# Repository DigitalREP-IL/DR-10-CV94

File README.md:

This is a tile-able design to drive a 25-pixel matrix of Cree CV-94 LED clusters. These are typically used in outdoor and longer distance applications, so the visual separation of the R,G, and B LEDs is not noticeable. The board is laid out such that four can be clustered together and maintain a regular pixel spacing. The onboard driver is I2C addressable but not pre-programmed so an external controller is necessary. Example code for the Arduino environment (easily portable to other frameworks) on a Raspberry Pi Pico (RP2040) is available.

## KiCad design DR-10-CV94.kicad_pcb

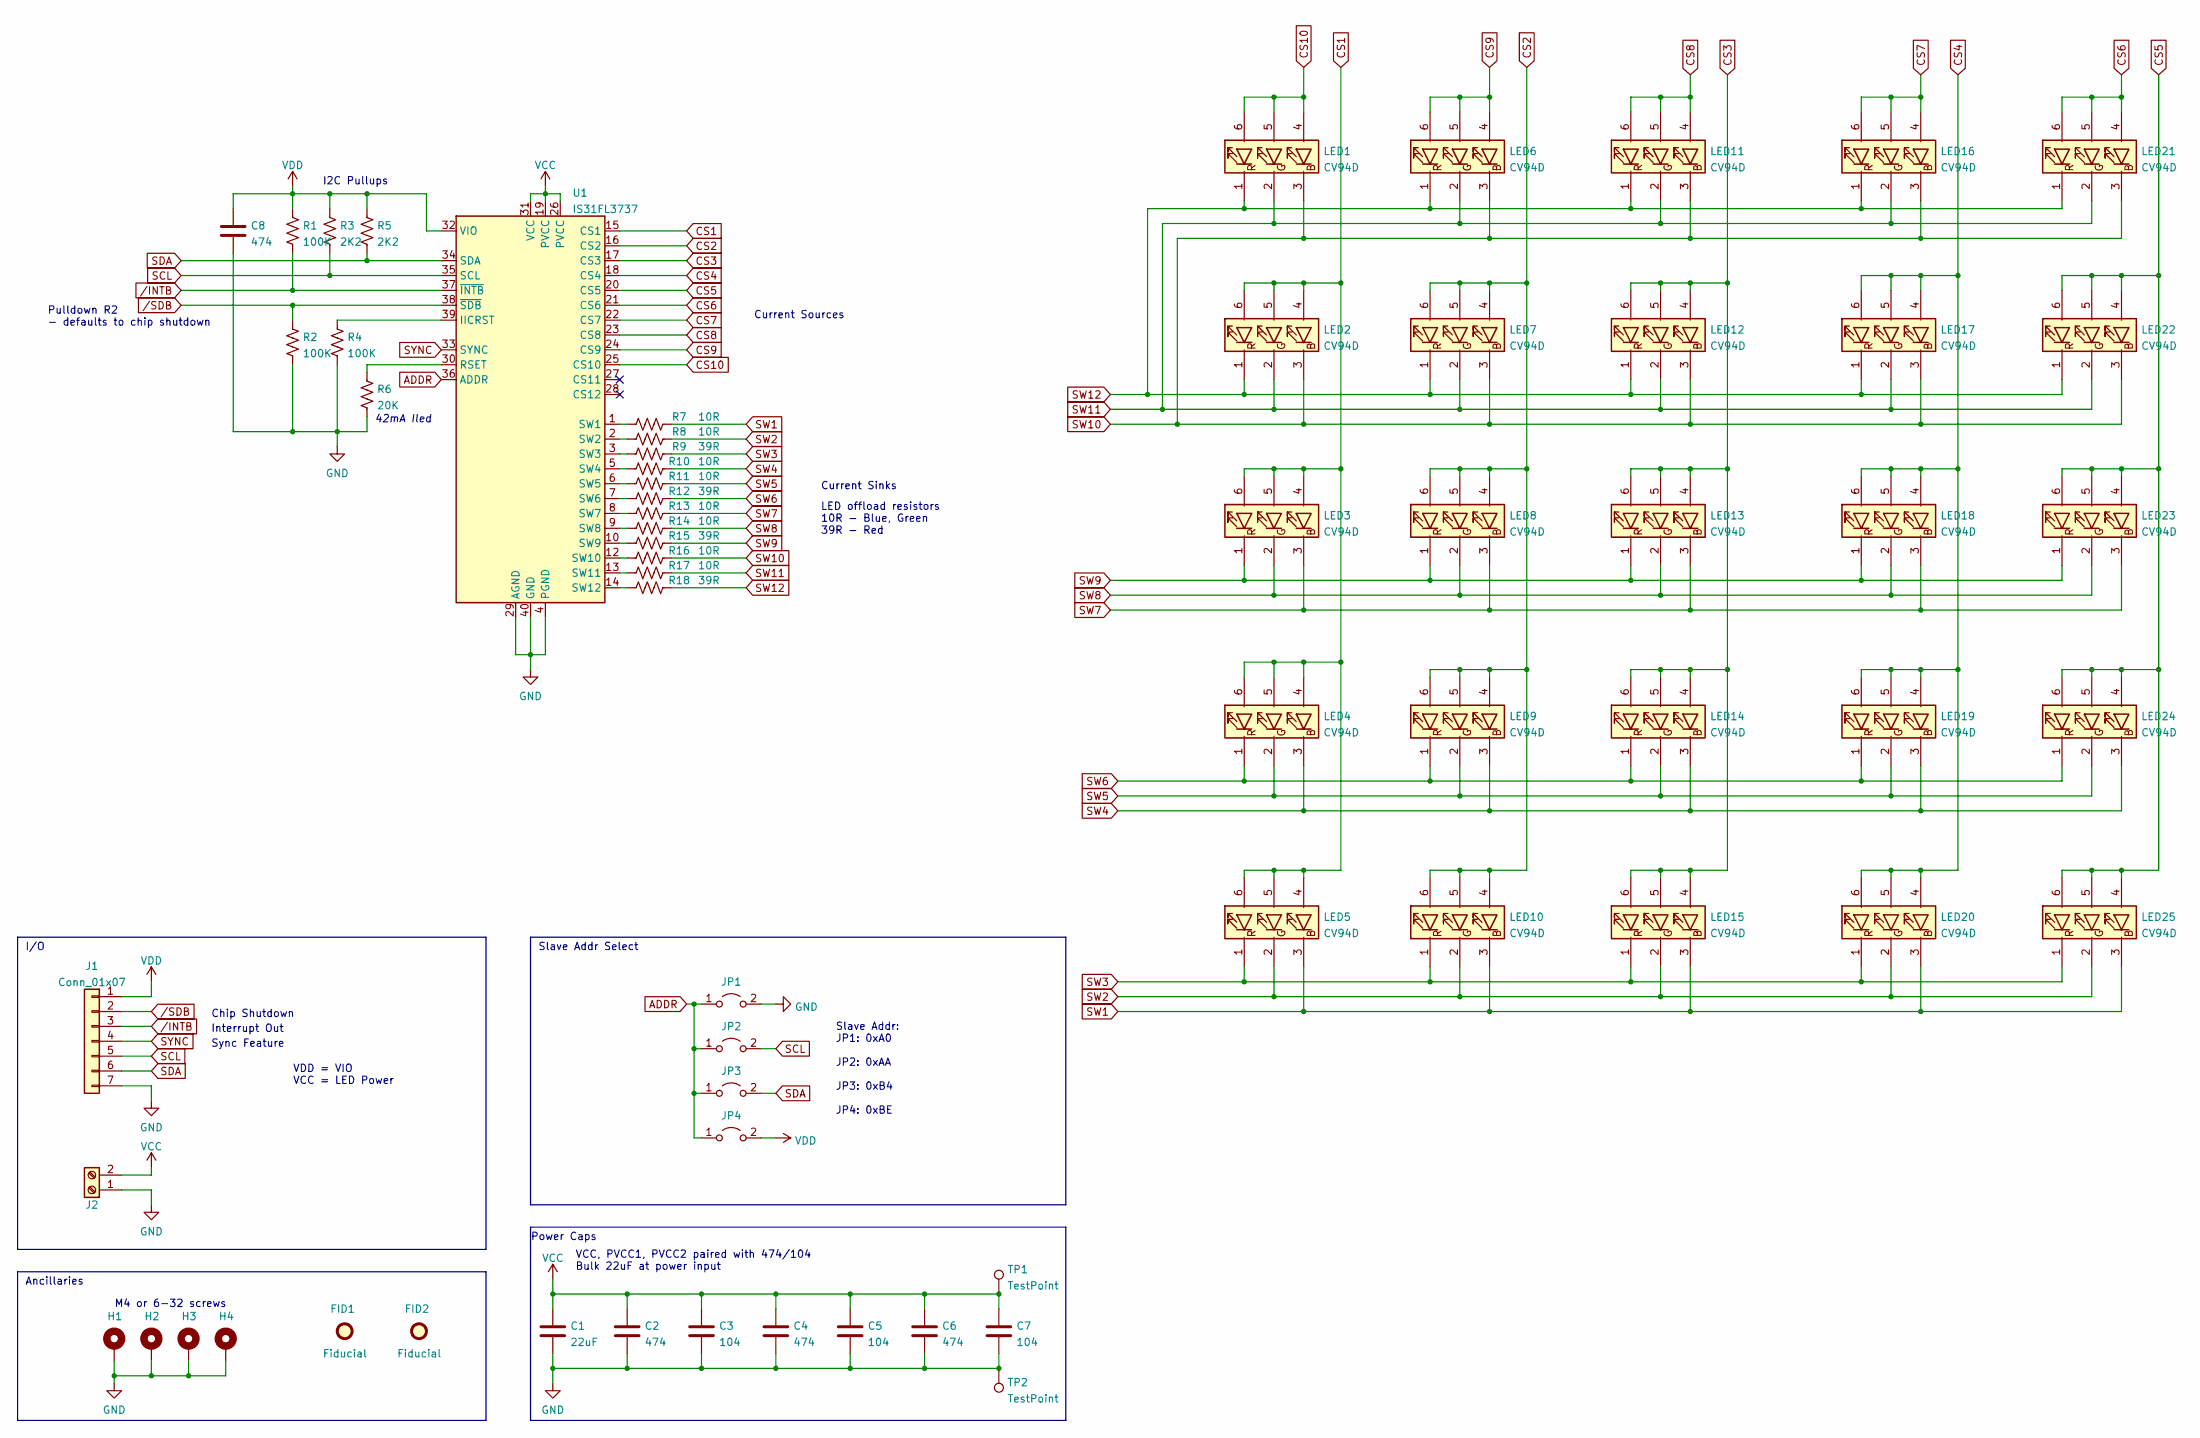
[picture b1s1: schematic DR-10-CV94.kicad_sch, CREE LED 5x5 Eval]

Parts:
C1: 22uF; CP_Elec_4x4.5
C2, C4, C6, C8: 474; C_0805_2012Metric
C3, C5, C7: 104; C_0805_2012Metric
FID1, FID2: Fiducial; Fiducial_0.5mm_Mask1mm
H1, H2, H3, H4: MountingHole_Pad; MountingHole_4.3mm_M4_ISO7380_Pad_TopBottom
J1: Conn_01x07; PinHeader_1x07_P2.54mm_Horizontal
J2: Screw_Terminal_01x02; TerminalBlock_Phoenix_MPT-0,5-2-2.54_1x02_P2.54mm_Horizontal
JP1, JP2, JP3, JP4: Jumper_2_Open; PinHeader_1x02_P2.54mm_Vertical
LED1, LED2, LED3, LED4, LED5, LED6, LED7, LED8, LED9, LED10, LED11, LED12, LED13, LED14, LED15, LED16, LED17, LED18, LED19, LED20, LED21, LED22, LED23, LED24, LED25: CV94D; LED_CREE_PLCC6_3n1
R1, R2, R4: 100K; R_0603_1608Metric
R3, R5: 2K2; R_0603_1608Metric
R6: 20K; R_0805_2012Metric
R7, R8, R10, R11, R13, R14, R16, R17: 10R; R_0603_1608Metric
R9, R12, R15, R18: 39R; R_0603_1608Metric
TP1, TP2: TestPoint; TestPoint_Pad_D2.5mm
U1: IS31FL3737; QFN-40-1EP_5x5mm_P0.4mm_EP3.8x3.8mm

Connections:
ADDR: JP1.1 (A), JP2.1 (A), JP3.1 (A), JP4.1 (A), U1.36 (ADDR)
CS1: LED2.4 (BA), LED2.5 (GA), LED2.6 (RA), LED3.4 (BA), LED3.5 (GA), LED3.6 (RA), LED4.4 (BA), LED4.5 (GA), LED4.6 (RA), LED5.4 (BA), LED5.5 (GA), LED5.6 (RA), U1.15 (CS1)
CS2: LED7.4 (BA), LED7.5 (GA), LED7.6 (RA), LED8.4 (BA), LED8.5 (GA), LED8.6 (RA), LED9.4 (BA), LED9.5 (GA), LED9.6 (RA), LED10.4 (BA), LED10.5 (GA), LED10.6 (RA), U1.16 (CS2)
CS3: LED12.4 (BA), LED12.5 (GA), LED12.6 (RA), LED13.4 (BA), LED13.5 (GA), LED13.6 (RA), LED14.4 (BA), LED14.5 (GA), LED14.6 (RA), LED15.4 (BA), LED15.5 (GA), LED15.6 (RA), U1.17 (CS3)
CS4: LED17.4 (BA), LED17.5 (GA), LED17.6 (RA), LED18.4 (BA), LED18.5 (GA), LED18.6 (RA), LED19.4 (BA), LED19.5 (GA), LED19.6 (RA), LED20.4 (BA), LED20.5 (GA), LED20.6 (RA), U1.18 (CS4)
CS5: LED22.4 (BA), LED22.5 (GA), LED22.6 (RA), LED23.4 (BA), LED23.5 (GA), LED23.6 (RA), LED24.4 (BA), LED24.5 (GA), LED24.6 (RA), LED25.4 (BA), LED25.5 (GA), LED25.6 (RA), U1.20 (CS5)
CS6: LED21.4 (BA), LED21.5 (GA), LED21.6 (RA), U1.21 (CS6)
CS7: LED16.4 (BA), LED16.5 (GA), LED16.6 (RA), U1.22 (CS7)
CS8: LED11.4 (BA), LED11.5 (GA), LED11.6 (RA), U1.23 (CS8)
CS9: LED6.4 (BA), LED6.5 (GA), LED6.6 (RA), U1.24 (CS9)
CS10: LED1.4 (BA), LED1.5 (GA), LED1.6 (RA), U1.25 (CS10)
GND: C1.2, C2.2, C3.2, C4.2, C5.2, C6.2, C7.2, C8.2, H1.1, H2.1, H3.1, H4.1, J1.7, J2.1, JP1.2 (B), R2.2, R4.2, R6.2, TP2.1, U1.4 (PGND), U1.11 (PGND), U1.29 (AGND), U1.40 (GND), U1.41 (GND)
unnamed: R4.1, U1.39 (IICRST)
unnamed: R6.1, U1.30 (RSET)
unnamed: R7.1, U1.1 (SW1)
unnamed: R8.1, U1.2 (SW2)
unnamed: R9.1, U1.3 (SW3)
unnamed: R10.1, U1.5 (SW4)
unnamed: R11.1, U1.6 (SW5)
unnamed: R12.1, U1.7 (SW6)
unnamed: R13.1, U1.8 (SW7)
unnamed: R14.1, U1.9 (SW8)
unnamed: R15.1, U1.10 (SW9)
unnamed: R16.1, U1.12 (SW10)
unnamed: R17.1, U1.13 (SW11)
unnamed: R18.1, U1.14 (SW12)
SCL: J1.5, JP2.2 (B), R3.2, U1.35 (SCL)
SDA: J1.6, JP3.2 (B), R5.2, U1.34 (SDA)
SW1: LED5.3 (BK), LED10.3 (BK), LED15.3 (BK), LED20.3 (BK), LED25.3 (BK), R7.2
SW2: LED5.2 (GK), LED10.2 (GK), LED15.2 (GK), LED20.2 (GK), LED25.2 (GK), R8.2
SW3: LED5.1 (RK), LED10.1 (RK), LED15.1 (RK), LED20.1 (RK), LED25.1 (RK), R9.2
SW4: LED4.3 (BK), LED9.3 (BK), LED14.3 (BK), LED19.3 (BK), LED24.3 (BK), R10.2
SW5: LED4.2 (GK), LED9.2 (GK), LED14.2 (GK), LED19.2 (GK), LED24.2 (GK), R11.2
SW6: LED4.1 (RK), LED9.1 (RK), LED14.1 (RK), LED19.1 (RK), LED24.1 (RK), R12.2
SW7: LED3.3 (BK), LED8.3 (BK), LED13.3 (BK), LED18.3 (BK), LED23.3 (BK), R13.2
SW8: LED3.2 (GK), LED8.2 (GK), LED13.2 (GK), LED18.2 (GK), LED23.2 (GK), R14.2
SW9: LED3.1 (RK), LED8.1 (RK), LED13.1 (RK), LED18.1 (RK), LED23.1 (RK), R15.2
SW10: LED1.3 (BK), LED2.3 (BK), LED6.3 (BK), LED7.3 (BK), LED11.3 (BK), LED12.3 (BK), LED16.3 (BK), LED17.3 (BK), LED21.3 (BK), LED22.3 (BK), R16.2
SW11: LED1.2 (GK), LED2.2 (GK), LED6.2 (GK), LED7.2 (GK), LED11.2 (GK), LED12.2 (GK), LED16.2 (GK), LED17.2 (GK), LED21.2 (GK), LED22.2 (GK), R17.2
SW12: LED1.1 (RK), LED2.1 (RK), LED6.1 (RK), LED7.1 (RK), LED11.1 (RK), LED12.1 (RK), LED16.1 (RK), LED17.1 (RK), LED21.1 (RK), LED22.1 (RK), R18.2
SYNC: J1.4, U1.33 (SYNC)
VCC: C1.1, C2.1, C3.1, C4.1, C5.1, C6.1, C7.1, J2.2, TP1.1, U1.19 (PVCC), U1.26 (PVCC), U1.31 (VCC)
VDD: C8.1, J1.1, JP4.2 (B), R1.1, R3.1, R5.1, U1.32 (VIO)
/INTB: J1.3, R1.2, U1.37 (~INTB)
/SDB: J1.2, R2.1, U1.38 (~SDB)

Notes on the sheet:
LED offload resistors 10R - Blue, Green 39R - Red
Slave Addr: JP1: 0xA0 JP2: 0xAA JP3: 0xB4 JP4: 0xBE
Sync Feature
Interrupt Out
I/O
Power Caps
Pulldown R2 - defaults to chip shutdown
Ancillaries
Current Sinks
42mA Iled
VCC, PVCC1, PVCC2 paired with 474/104 Bulk 22uF at power input
M4 or 6-32 screws
I2C Pullups
Current Sources
Chip Shutdown
VDD = VIO VCC = LED Power
Slave Addr Select

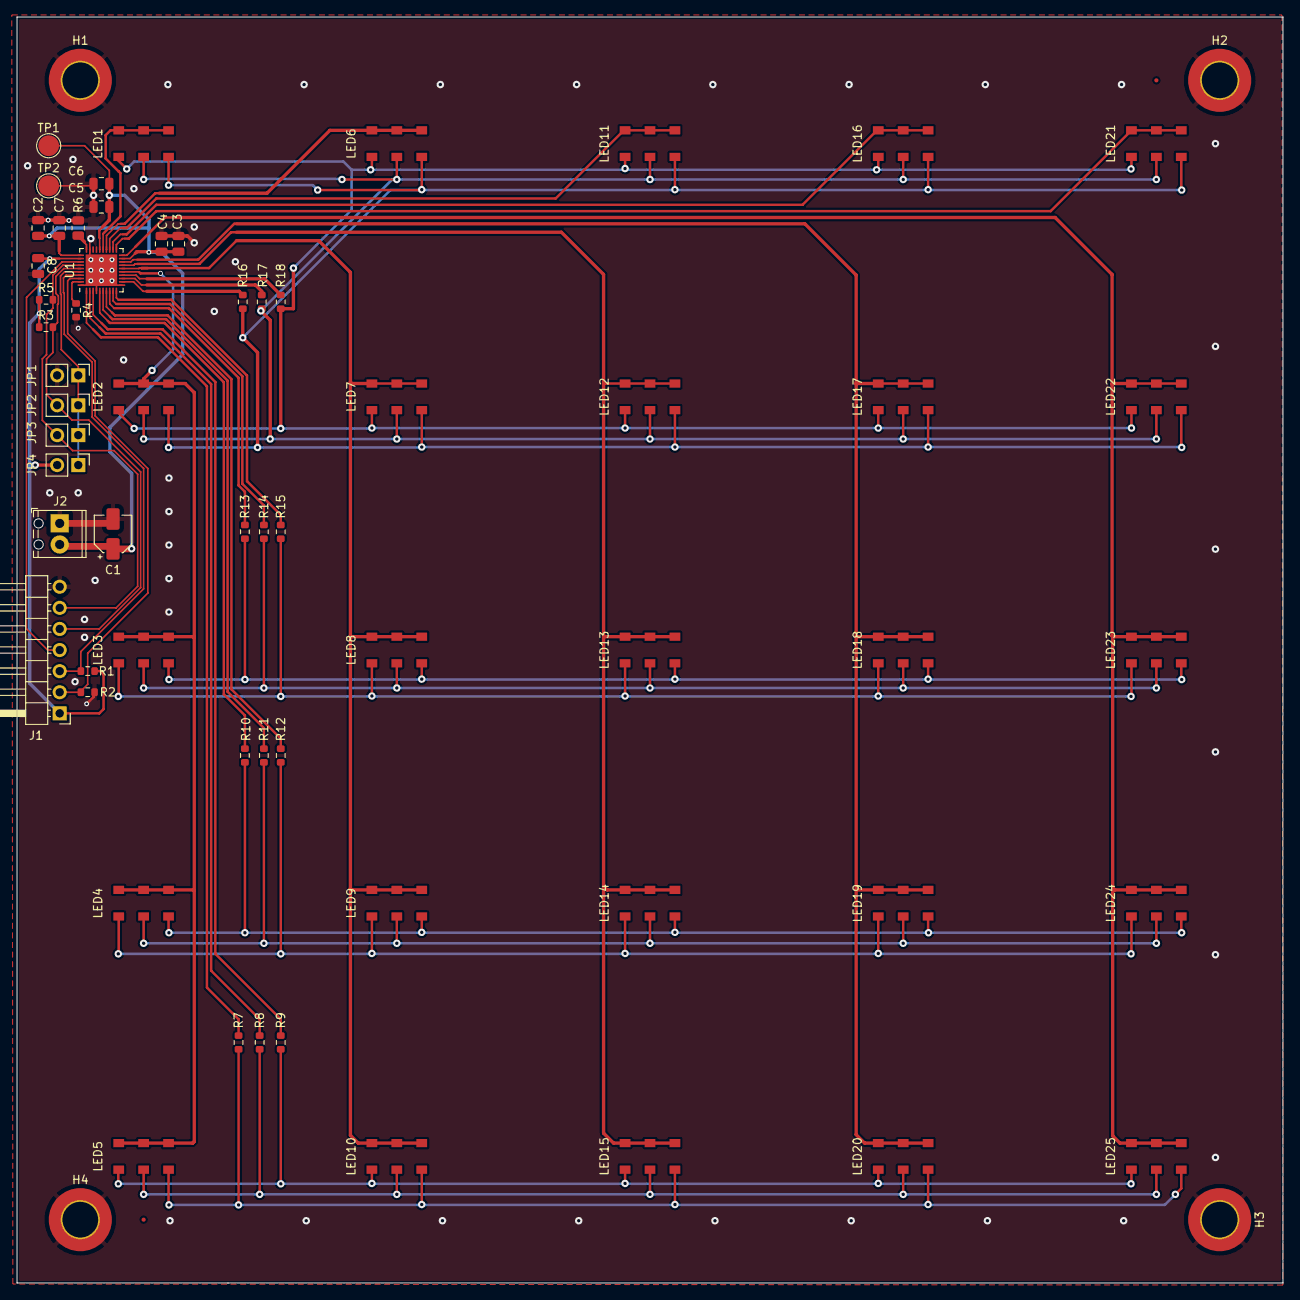
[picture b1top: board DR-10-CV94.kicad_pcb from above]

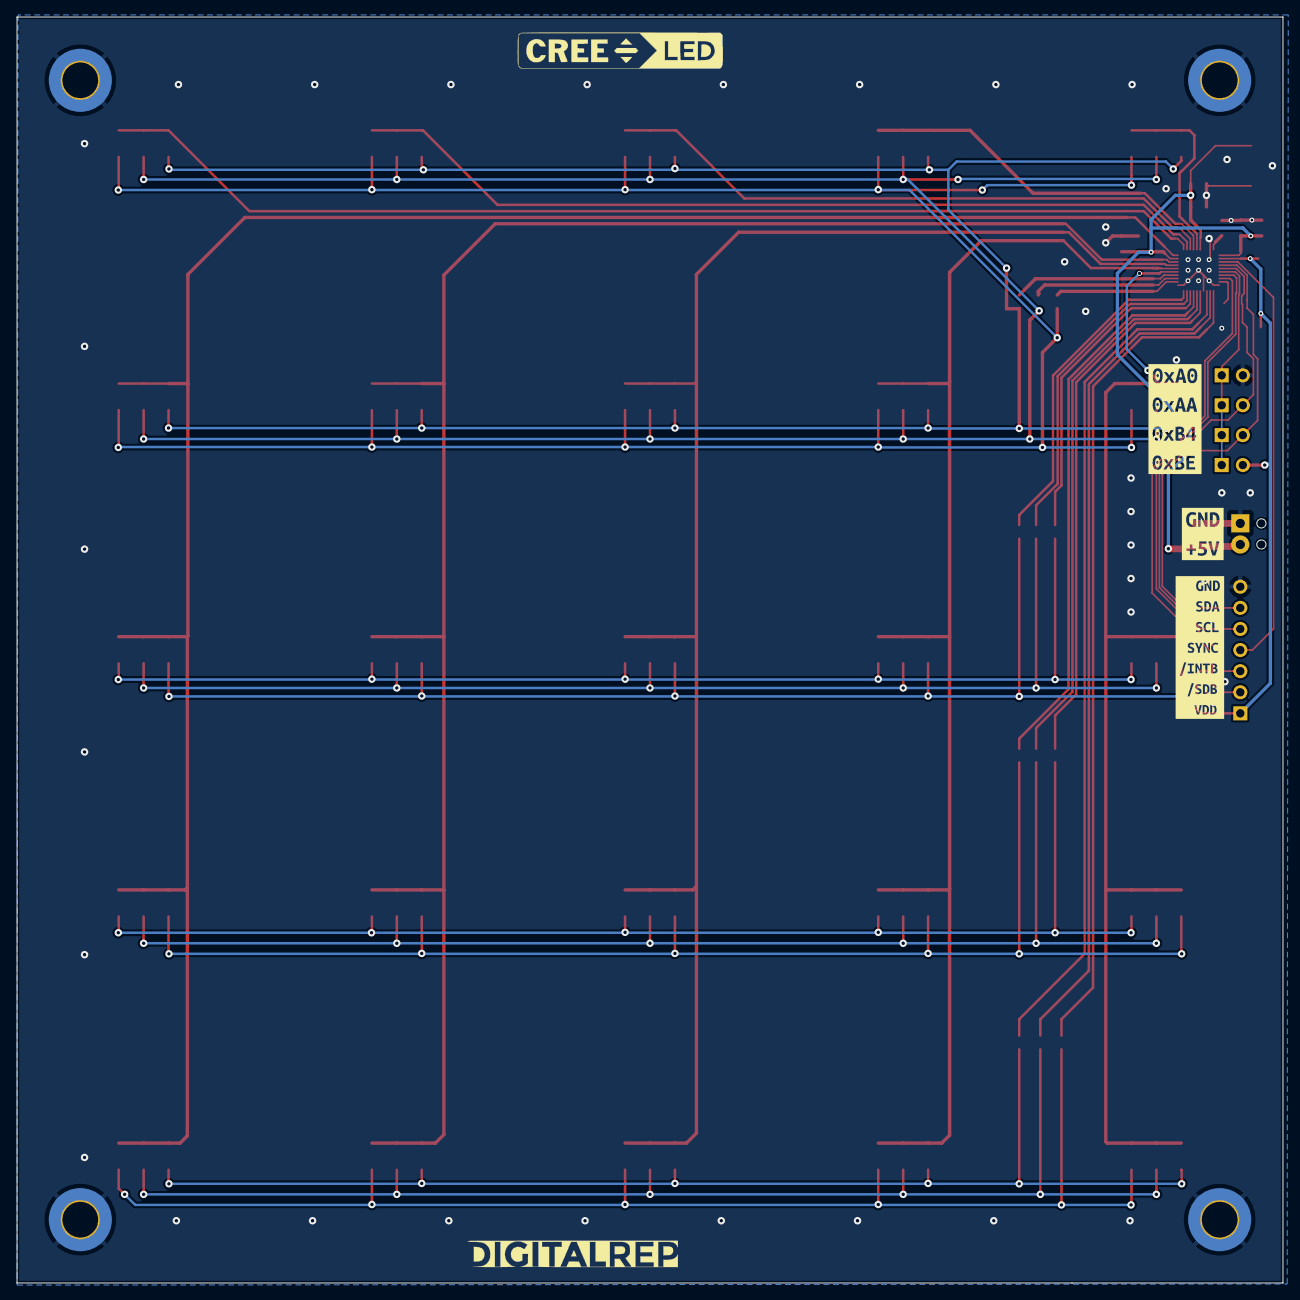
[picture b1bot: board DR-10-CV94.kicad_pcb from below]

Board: 2 copper layers, 152.4 x 152.4 mm, 69 parts (3 on the bottom side), 45 nets.

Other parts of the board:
kibuzzard-63458A05: G***; kibuzzard-63458A05
kibuzzard-634588F2: G***; kibuzzard-634588F2
kibuzzard-6345892A: G***; kibuzzard-6345892A

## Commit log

2024-03-20 adding Arduino archive
